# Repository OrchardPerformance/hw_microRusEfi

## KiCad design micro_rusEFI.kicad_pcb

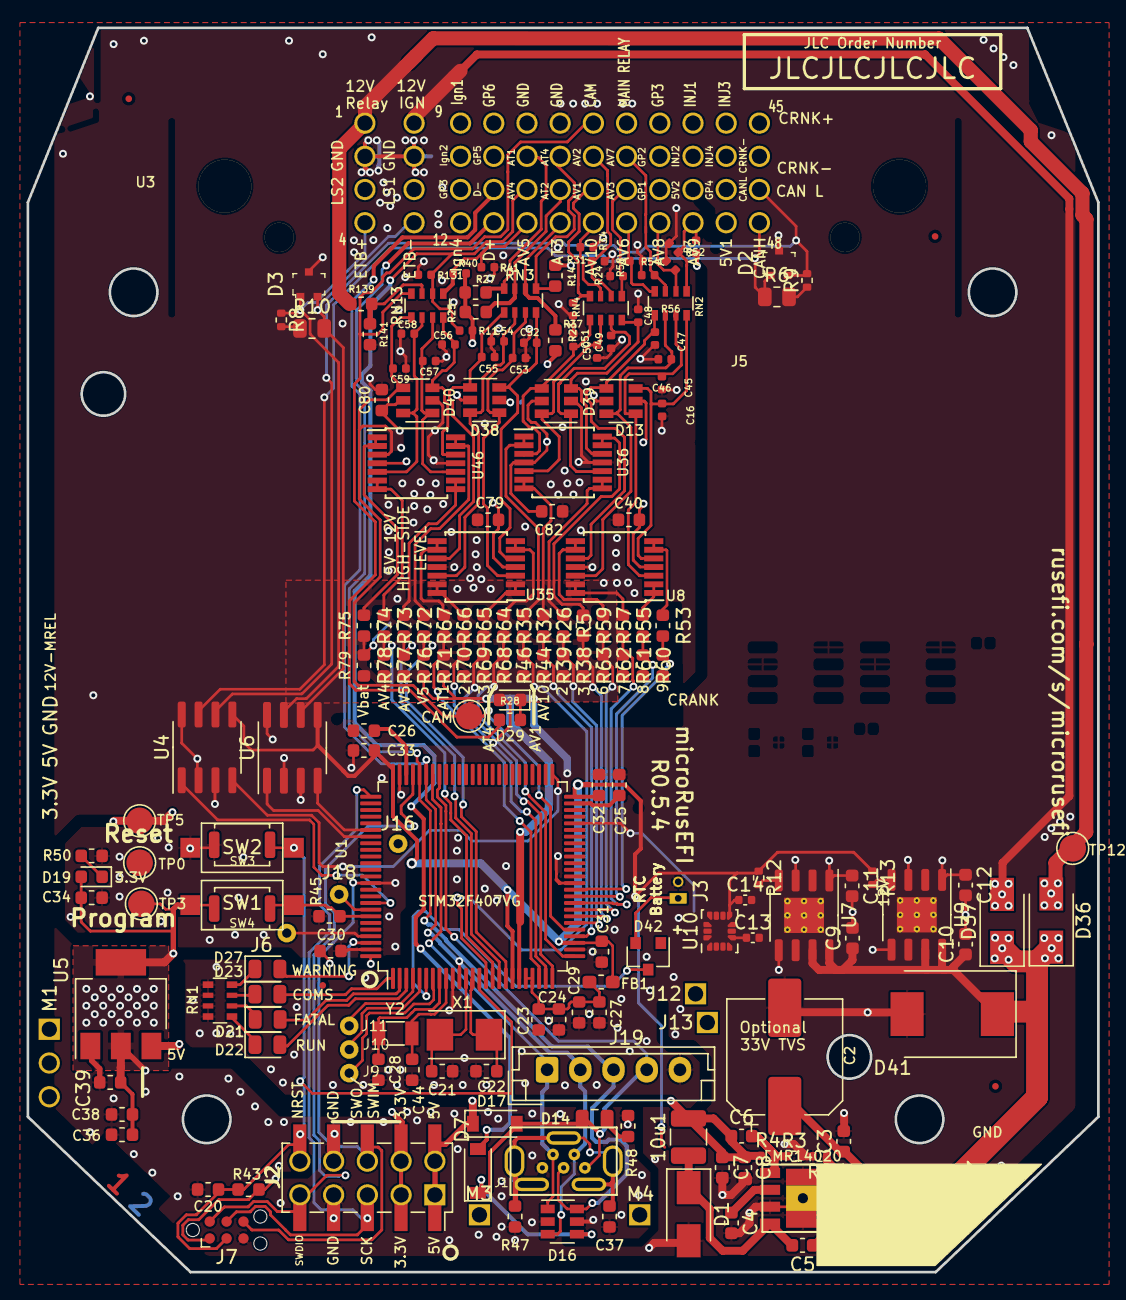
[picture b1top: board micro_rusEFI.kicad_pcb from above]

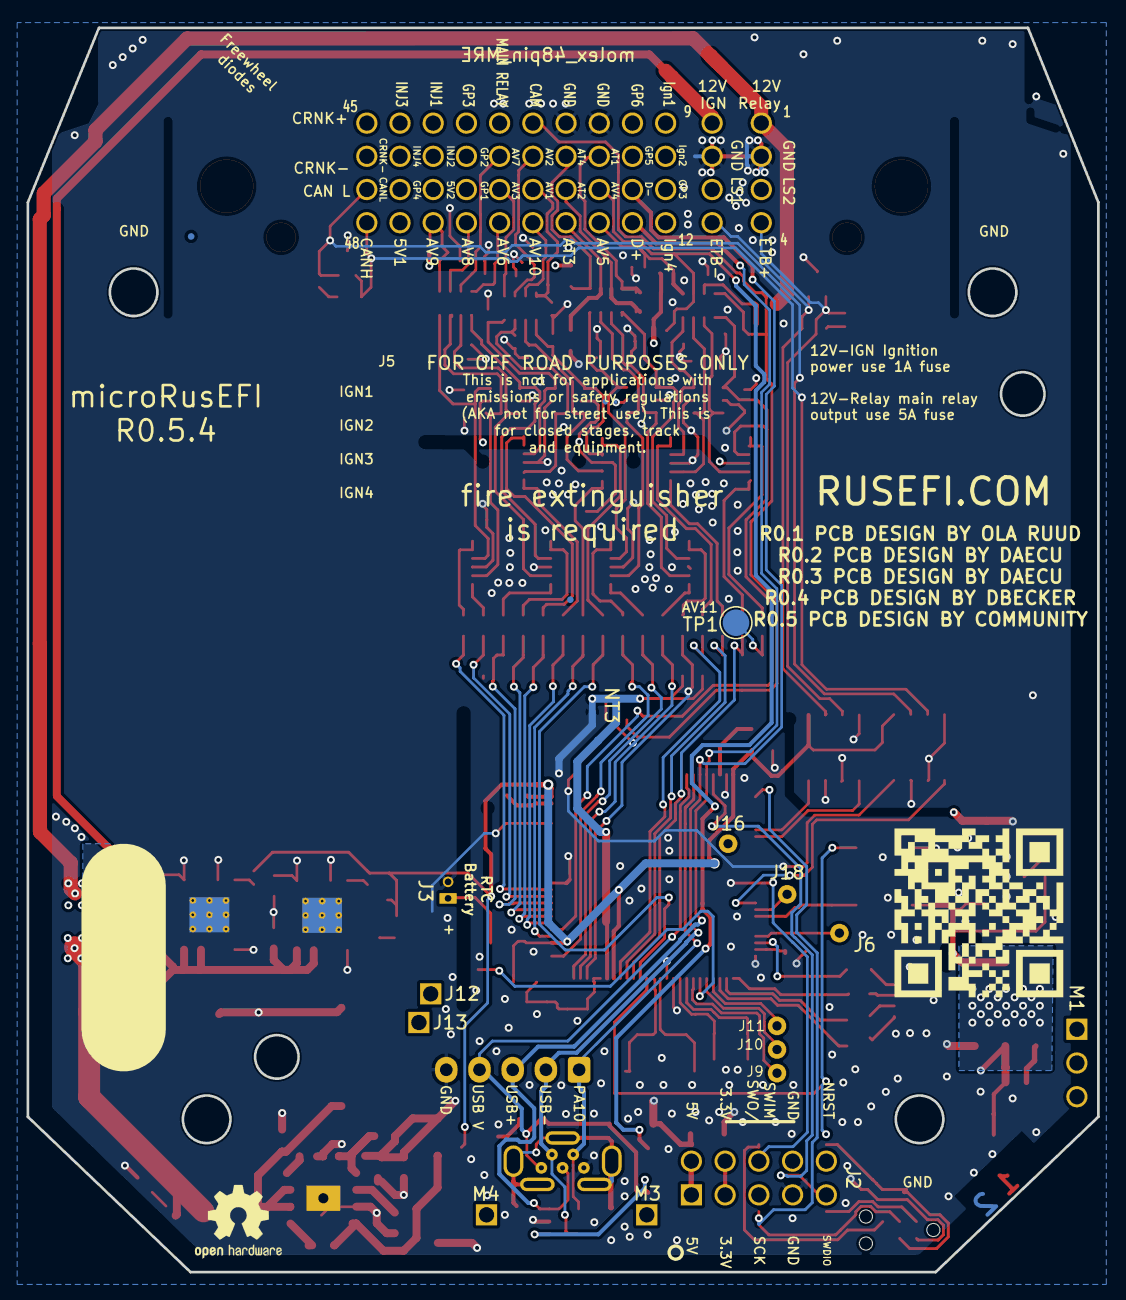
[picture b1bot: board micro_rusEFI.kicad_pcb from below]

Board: 4 copper layers, 80.6 x 93.7 mm, 191 parts (7 on the bottom side), 130 nets.

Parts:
2.2u1: INDUCTOR; MWSA0503
10u1: L_Small; L_1210_3225Metric
C1: 4.7u; C_0603_1608Metric
C2: 100UF 50V; CP_Elec_8x10.5
C3, C9, C10, C11, C12: 1u; C_0603_1608Metric
C4: 10n; C_0603_1608Metric
C5: 100n; C_0603_1608Metric
C6: 270p; C_0603_1608Metric
C7, C8: 10u; C_0603_1608Metric
C13, C14, C16, C45, C46, C47, C48, C49, C50, C51, C52, C53, C54, C55, C56, C57, C58, C59: 100nF; C_0402_1005Metric
C20, C29, C40, C79, C80, C82: 10nF; C_0603_1608Metric
C21, C22: 18pF; C_0603_1608Metric
C23, C27, C36: 1uF; C_0603_1608Metric
C24, C30, C31, C32, C33, C34, C37, C38: 100nF; C_0603_1608Metric
C25, C26: 2.2uF; C_0603_1608Metric
C28, C44: 6.8pF; C_0603_1608Metric
C39: 22uF; C_0603_1608Metric
D1: D_Schottky; D_SMA
D2, D3: PESD1CAN-UX; SOT-323
D7, D17: B5819W; D_SOD-123
D13, D16, D38, D39, D40: SRV05-4; SOT-23-6
D14: LED-GREEN; C_0805_2012Metric
D19, D29: LED-RED; LED_0603_1608Metric
D21: LED-RED; LED_0805_2012Metric
D22: LED-GREEN; LED_0805_2012Metric
D23: LED-BLUE; LED_0805_2012Metric
D27: LED-YELLOW; LED_0805_2012Metric
D36, D37: SS54; D_SMA
D41: SM15T33C; D_SMC
D42: BAV70; SOT-23
FB1: FILTER; R_0603_1608Metric_Pad1.05x0.95mm_HandSolder
FID1, FID2, FID3, FID4, FID5, FID6: Fiducial; Fiducial_0.5mm_Mask1mm
G1: Disclaimer; Off_Road_Disclaimer
J1: USB_B_Micro; MINI-USB_RCTP_V-T_B_and_HW-MU-5F-23
J2: Conn_02x05_Odd_Even; PinSocket_2x05_P2.54mm_Vertical_SMD
J7: TC2030; Tag-Connect_TC2030-IDC-NL_2x03_P1.27mm_Vertical
J19: Conn_01x06; JST_EH_B5B-EH-A_1x05_P2.50mm_Vertical
LOGO1: DNP; OSHW-Logo2_7.3x6mm_SilkScreen
LOGO3: LOGO; MRE_QR_code
NT1, NT2: Net-Tie_2; Net-Tie_2_8.5mil
NT3: Analog Ground Net Tie; NetTie-2_SMD_Pad0.5mm
R1: 1; R_0402_1005Metric
R2, R12, R13: 10k; R_0402_1005Metric
R3: 12k; R_0402_1005Metric
R4: 68k; R_0402_1005Metric
R5, R26, R32, R35, R53, R55, R57, R59, R64, R65, R66, R67, R72, R73, R74, R75: 6.8K; R_0603_1608Metric
R6, R10: 120; R_0805_2012Metric
R7, R11, R40: DNP; R_0402_1005Metric
R8, R9: 0; R_0402_1005Metric
R14, R23, R25, R27: 2.7k; R_0603_1608Metric
R24, R31, R34, R37, R41, R52, R54, R56, R58, R131: 470K; R_0402_1005Metric
R28, R48: 2.2k; R_0603_1608Metric
R38, R39, R43, R44, R45, R46, R60, R61, R62, R63, R68, R69, R70, R71, R76, R77, R78, R79, R141: 10K; R_0603_1608Metric
R47: 100K; R_0603_1608Metric
R50: 1k; R_0603_1608Metric
R139: 39k; R_0603_1608Metric
RN1: 1k; R_Array_Convex_4x0603
RN2, RN3, RN4, RN13: 10k; R_Array_Convex_4x0603
SW1, SW2: SW_Push; SW_SPST_CK_RS282G05A3
SW3, SW4: SW_Push; SW_Push_SPST_NO_Alps_SKRK
TP0, TP3: GND; TestPoint_Pad_D2.0mm
TP1, TP2: TP; TestPoint_Pad_D2.0mm
TP5, TP12: 5V; TestPoint_Pad_D2.0mm
U1: STM32F427VGT6; LQFP-100_14x14mm_P0.5mm
U2: LMR14020; SOIC8-DFN
U3: molex_48pin_MRE; Molex_48_BCM
U4, U6: TJA1051T-3; SOIC-8_3.9x4.9mm_P1.27mm
U5: LM1117-3.3; SOT-223-3_TabPin2
U7, U9: TLS115; Infineon_PG-DSO-8-27_3.9x4.9mm_EP2.65x3mm_ThermalVias
U8, U35, U36, U46: MCP6004; TSSOP-14_4.4x5mm_P0.65mm
U10: LSM6DS3; LGA-14_3x2.5mm_P0.5mm_LayoutBorder3x4y
X1: 8MHz 20pF; Crystal_SMD_5032-2Pin_5.0x3.2mm
Y2: 32768 Hz; Crystal_SMD_3215-2Pin_3.2x1.5mm

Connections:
5V: 10u1.2, C6.1, C7.1, C8.1, C40.1, C79.1, C80.1, C82.1, D13.5, D16.5, D17.1 (K), D29.2 (A), D38.5, D39.5, D40.5, J2.1, J2.2, R4.1, R7.1, R11.2, R14.2, R23.2, R25.2, R27.2, R40.2, TP5.1, U3.J201, U3.J202, U4.3 (VCC), U5.3 (VI), U6.3 (VCC), U7.5 (ADJ), U8.4 (V+), U9.5 (ADJ), U35.4 (V+), U36.4 (V+), U46.4 (V+)
5V1: C12.1, U3.44, U9.1 (OUT)
5V2: C11.1, U3.39, U7.1 (OUT)
/12V_KEY: D37.2 (A), U3.5
/12V_MREL: D36.2 (A), R139.2, TP12.1, U3.1
/12V_SAFE: 2.2u1.1, C9.1, C10.1, D36.1 (K), D37.1 (K), D41.1 (A1), R1.1, U7.7 (EN), U7.8 (IN), U9.7 (EN), U9.8 (IN)
/ADC/AGND: NT3.2, R38.1, R39.1, R44.1, R46.1, R60.1, R61.1, R62.1, R63.1, R68.1, R69.1, R70.1, R71.1, R76.1, R77.1, R78.1, R79.1, U1.20 (VSSA)
/ADC/AV11_MCU: R75.1, R79.2, TP1.1
/AT1: R27.1, RN3.4 (R4.1), U3.18
/AT1_MCU: R67.1, R71.2, U1.23 (PA0)
/AT2: R25.1, RN3.3 (R3.1), U3.23
/AT2_MCU: R66.1, R70.2, U1.24 (PA1)
/AT3: R23.1, RN3.2 (R2.1), U3.24
/AT3_MCU: R65.1, R69.2, U1.25 (PA2)
/AT4: R14.1, RN3.1 (R1.1), U3.22
/AT4_MCU: R64.1, R68.2, U1.26 (PA3)
/AV1: R37.1, RN4.4 (R4.1), U3.27
/AV1_MCU: R35.1, R46.2, U1.15 (PC0)
/AV2: R31.1, RN4.2 (R2.1), U3.26
/AV2_MCU: R26.1, R39.2, U1.31 (PA6)
/AV3: R24.1, RN4.1 (R1.1), U3.31
/AV3_MCU: R5.1, R38.2, U1.32 (PA7)
/AV4: D7.2 (A), R11.1, R131.1, RN13.2 (R2.1), U3.19
/AV4_MCU: R73.1, R77.2, U1.17 (PC2)
/AV5: R40.1, R41.1, RN13.1 (R1.1), U3.20
/AV5_MCU: R72.1, R76.2, U1.18 (PC3)
/AV6: R58.1, RN2.4 (R4.1), U3.32
/AV6_MCU: R59.1, R63.2, U1.33 (PC4)
/AV7: R56.1, RN2.3 (R3.1), U3.30
/AV7_MCU: R57.1, R62.2, U1.34 (PC5)
/AV8: R54.1, RN2.2 (R2.1), U3.36
/AV8_MCU: R55.1, R61.2, U1.35 (PB0)
/AV9: R7.2, R52.1, RN2.1 (R1.1), U3.40
/AV9_MCU: R53.1, R60.2, U1.36 (PB1)
/AV10: R34.1, RN4.3 (R3.1), U3.28
/AV10_MCU: R32.1, R44.2, U1.29 (PA4)
/CAM_MCU: C59.1, D40.4, RN13.5 (R4.2), TP2.1, U1.30 (PA5), U46.3 (+)
/CAM_SENSOR: R28.1, RN13.4 (R4.1), U3.25
/CAN Transceiver/CANH1: D2.1 (C1), R6.1, U4.7 (CANH)
/CAN Transceiver/CANH2: D3.1 (C1), R8.1, U6.7 (CANH)
/CAN Transceiver/CANL1: D2.2 (C2), R9.2, U4.6 (CANL)
/CAN Transceiver/CANL2: D3.2 (C2), R10.2, U6.6 (CANL)
/MCU/BOOT0: R45.1, SW1.2, SW4.2, U1.94 (BOOT0)
/MCU/PA9: D7.1 (K), D14.2 (A), D16.4, D17.2 (A), J1.1 (VBUS), J19.4, NT1.2
/MCU/PA10: D16.1, J1.4 (ID), J19.1, U1.69 (PA10)
/MCU/PA13: J2.9, J7.2, U1.72 (PA13), U3.J209
/MCU/PA14: J2.5, J7.4, U1.76 (PA14), U3.J205
/MCU/PB2-BOOT1: NT2.2, U1.37 (PB2)
/MCU/PB3: J2.6, J7.6, U3.J206
/MCU/PB7: U1.93 (PB7), U3.J18
/MCU/PD0: U1.81 (PD0), U3.J16
/MCU/PE5: U1.4 (PE5), U3.J11
/MCU/PE6: U1.5 (PE6), U3.J10
/MCU/VDDA: C23.2, C24.2, C27.2, C29.2, FB1.2, U1.21 (VREF+), U1.22 (VDDA)
/MCU/Vrtc: D42.2 (A), U3.J31
/MCU/Vrtcc: D42.3 (K), U1.6 (VBAT)
/MCU/shield: C37.1, J1.6 (Shield), R47.1
/PB10: U1.47 (PB10), U3.J13
/PB11: U1.48 (PB11), U3.J12
/PC13: U1.7 (PC13), U3.J9
/PE0: U1.97 (PE0), U3.J6
/PE1: D27.2 (A), U1.98 (PE1)
/PE2: D23.2 (A), U1.1 (PE2)
/PE3: D21.2 (A), U1.2 (PE3)
/PE4: D22.2 (A), U1.3 (PE4)
/RST: C20.2, J2.10, J7.3, R43.2, SW2.1, SW3.1, U1.14 (NRST), U3.J210
/USB_D+: D16.6, J1.3 (D+), J19.3, U1.71 (PA12), U3.16
/USB_D-: D16.3, J1.2 (D-), J19.2, U1.70 (PA11), U3.15
/Vbat_MCU: R74.1, R78.2, U1.16 (PC1)
GND: C1.2, C2.2, C3.2, C4.2, C7.2, C8.2, C9.2, C10.2, C11.2, C12.2, C13.2, C14.2, C16.2, C20.1, C21.2, C22.2, C23.1, C24.1, C25.2, C26.2, C27.1, C28.2, C29.1, C30.1, C31.1, C32.1, C33.1, C34.1, C36.1, C37.2, C38.2, C39.1, C40.2, C44.1, C45.2, C46.2, C47.2, C48.2, C49.2, C50.2, C51.2, C52.2, C53.2, C54.2, C55.2, C56.2, C57.2, C58.2, C59.2, C79.2, C80.2, C82.2, D1.2 (A), D2.3 (C3), D3.3 (C3), D13.2, D16.2, D38.2, D39.2, D40.2, D41.2 (A2), J1.5 (GND), J2.7, J2.8, J7.5, J19.5, NT2.1, NT3.1, R2.2, R3.2, R24.2, R31.2, R34.2, R37.2, R41.2, R45.2, R47.2, R48.1, R50.1, R52.2, R54.2, R56.2, R58.2, R131.2, R141.2, RN1.5 (R4.2), RN1.6 (R3.2), RN1.7 (R2.2), RN1.8 (R1.2), SW2.2, SW3.2, TP0.1, U1.10 (VSS), U1.27 (VSS), U1.74 (VSS), U1.99 (VSS), U2.7 (GND), U2.9 (GND), U3.2, U3.6, U3.17, U3.21, U3.J32, U3.J207, U3.J208, U4.2 (GND), U4.8 (S), U5.1 (GND), U6.2 (GND), U6.8 (S), U7.3 (GND), U7.9 (GND), U8.11 (V-), U9.3 (GND), U9.9 (GND), U10.2 (SDX), U10.3 (SCX), U10.6 (GND), U10.7 (GND), U35.11 (V-), U36.11 (V-), U46.11 (V-)
unnamed: 2.2u1.2, C2.1, C3.1, U2.2 (VIN), U2.3 (EN)
unnamed: 10u1.1, C5.2, D1.1 (K), U2.8 (SW)
unnamed: C1.1, R1.2
unnamed: C4.1, U2.6 (SS)
unnamed: C5.1, U2.1 (BOOT)
unnamed: C6.2, R3.1, R4.2, U2.5 (FB)
unnamed: C13.1, U10.5 (VDDIO)
unnamed: C16.1, D13.6, RN2.8 (R1.2), U8.5 (+)
unnamed: C21.1, U1.12 (PH0), X1.2
unnamed: C22.1, U1.13 (PH1), X1.1
unnamed: C25.1, U1.49 (VCAP_1)
unnamed: C26.1, U1.73 (VCAP_2)
unnamed: C28.1, U1.8 (PC14), Y2.1
unnamed: C44.2, U1.9 (PC15), Y2.2
unnamed: C45.1, D13.4, RN2.7 (R2.2), U8.3 (+)
unnamed: C46.1, D13.3, RN2.6 (R3.2), U8.12 (+)
unnamed: C47.1, D13.1, RN2.5 (R4.2), U8.10 (+)
unnamed: C48.1, D39.3, RN4.8 (R1.2), U36.12 (+)
unnamed: C49.1, D39.1, RN4.7 (R2.2), U36.10 (+)
unnamed: C50.1, D39.6, RN4.6 (R3.2), U36.5 (+)
unnamed: C51.1, D39.4, RN4.5 (R4.2), U36.3 (+)
unnamed: C52.1, D38.6, RN3.8 (R1.2), U35.5 (+)
unnamed: C53.1, D38.4, RN3.7 (R2.2), U35.3 (+)
unnamed: C54.1, D38.3, RN3.6 (R3.2), U35.12 (+)
unnamed: C55.1, D38.1, RN3.5 (R4.2), U35.10 (+)
unnamed: C56.1, D40.3, RN13.8 (R1.2), U46.12 (+)
unnamed: C57.1, D40.1, RN13.7 (R2.2), U46.10 (+)
unnamed: C58.1, D40.6, RN13.6 (R3.2), U46.5 (+)
unnamed: D14.1 (K), R48.2
unnamed: D19.1 (K), R50.2
unnamed: D21.1 (K), RN1.2 (R2.1)
unnamed: D22.1 (K), RN1.1 (R1.1)
unnamed: D23.1 (K), RN1.3 (R3.1)
unnamed: D27.1 (K), RN1.4 (R4.1)
unnamed: D29.1 (K), R28.2
unnamed: NT1.1, U1.68 (PA9)
unnamed: R2.1, U2.4 (RT)
unnamed: R5.2, U36.13 (-), U36.14
unnamed: R6.2, R9.1
unnamed: R8.2, R10.1
unnamed: R12.2, U7.4 (PG)
unnamed: R13.2, U9.4 (PG)
unnamed: R26.2, U36.8, U36.9 (-)
unnamed: R32.2, U36.6 (-), U36.7
unnamed: R35.2, U36.1, U36.2 (-)
unnamed: R53.2, U8.6 (-), U8.7
unnamed: R55.2, U8.1, U8.2 (-)
unnamed: R57.2, U8.13 (-), U8.14
unnamed: R59.2, U8.8, U8.9 (-)
unnamed: R64.2, U35.6 (-), U35.7
unnamed: R65.2, U35.1, U35.2 (-)
unnamed: R66.2, U35.13 (-), U35.14
unnamed: R67.2, U35.8, U35.9 (-)
unnamed: R72.2, U46.13 (-), U46.14
unnamed: R73.2, U46.8, U46.9 (-)
unnamed: R74.2, U46.6 (-), U46.7
unnamed: R75.2, U46.1, U46.2 (-)
unnamed: R139.1, R141.1, RN13.3 (R3.1)
SCK: U1.89 (PB3), U10.13 (SCL)
VDD: C14.1, C30.2, C31.2, C32.2, C33.2, C34.2, C36.2, C38.1, C39.2, D19.2 (A), FB1.1, J2.3, J2.4, J7.1, R12.1, R13.1, R43.1, SW1.1, SW4.1, TP3.1, U1.11 (VDD), U1.19 (VDD), U1.28 (VDD), U1.50 (VDD), U1.75 (VDD), U1.100 (VDD), U3.J203, U3.J204, U4.5 (VIO), U5.2 (VO), U6.5 (VIO), U10.8 (VDD)

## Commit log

2022-01-25 did stuff
2022-01-29 arranging 5v
2022-01-30 5v stage improved
2022-01-30 Started CAN
2022-01-30 Added CAN x2
2022-01-30 Converted to 4 layer
2022-01-30 CAN complete
2022-01-30 bits
2022-02-01 Fixed CAN and 5v pads
2022-02-02 Fixing tags
2022-02-13 5v supplies added
2022-02-15 Work on 6 axis
